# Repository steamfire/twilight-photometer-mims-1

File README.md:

View this project on [CADLAB.io](https://cadlab.io/project/26619). 

# twilight-photometer-mims-1
 Simple version of Forrest Mims 1 channel DIY twilight photometer

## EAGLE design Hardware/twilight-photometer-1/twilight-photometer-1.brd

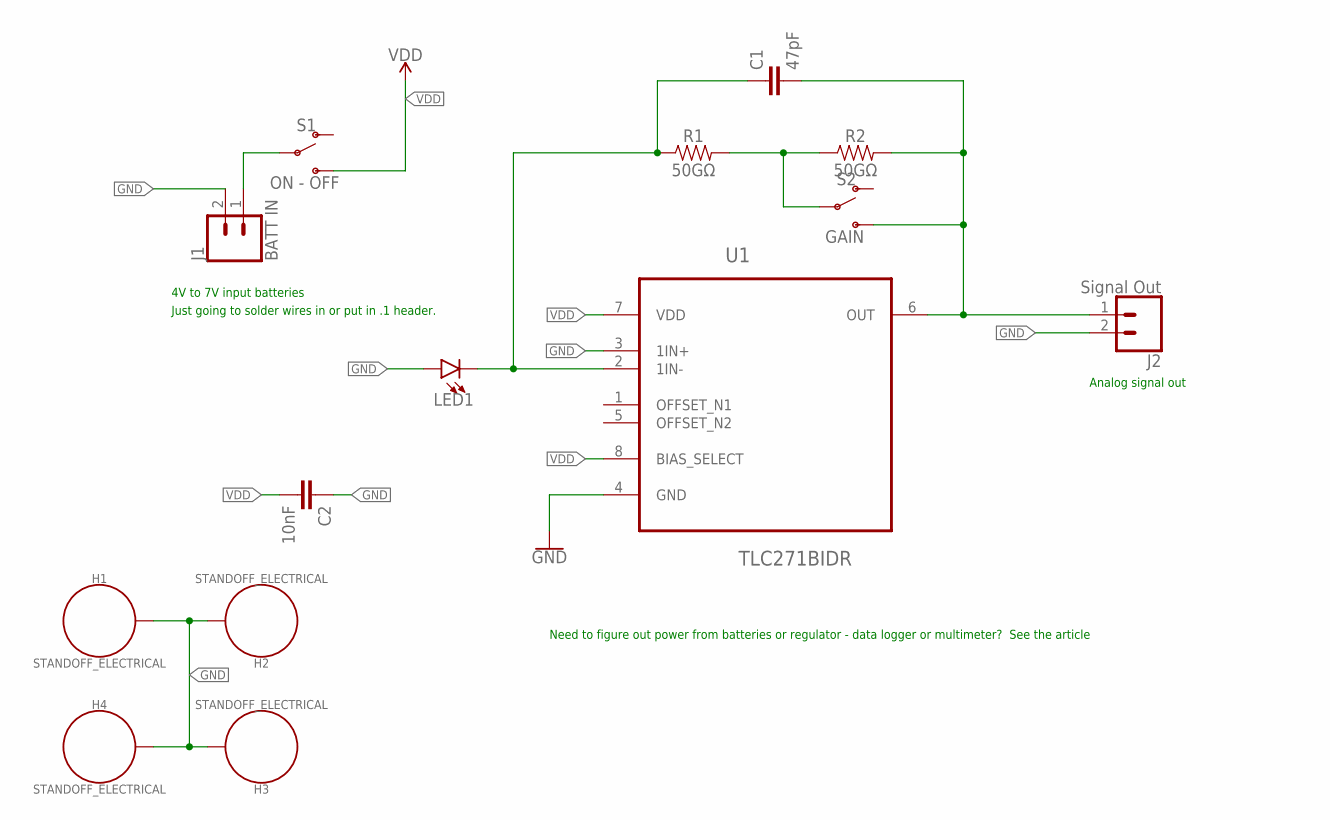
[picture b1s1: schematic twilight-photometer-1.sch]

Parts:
C1: 47pF; 0603
C2: 10nF; 0603
H1, H2, H3, H4: STANDOFF_ELECTRICAL; STANDOFF-ELECTRICAL
J1: BATT IN; 1X02_LOCK_LONGPADS
J2: Signal Out; 1X02_LOCK_LONGPADS
LED1: LED5MM; LED_5MM
R1, R2: 50GΩ; 0805
S1: ON - OFF; SWITCH_SPDT_PTH_11.6X4.0MM_LOCK
S2: GAIN; SWITCH_SPDT_PTH_11.6X4.0MM_LOCK
U1: TLC271BIDR; SOIC127P600X175-8N

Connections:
GND: C2.1, H1.P1, H2.P1, H3.P1, H4.P1, J1.2, J2.2, LED1.A, U1.3 (1IN+), U1.4 (GND)
unnamed: R1.2, R2.1, S2.2
unnamed: C1.1, LED1.K (C), R1.1, U1.2 (1IN-)
unnamed: J1.1, S1.2
unnamed: C1.2, J2.1, R2.2, S2.3 (S), U1.6 (OUT)
VDD: C2.2, S1.3 (S), U1.7 (VDD), U1.8 (BIAS_SELECT)

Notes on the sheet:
Need to figure out power from batteries or regulator - data logger or multimeter? See the article
4V to 7V input batteries
Just going to solder wires in or put in .1 header.
Analog signal out

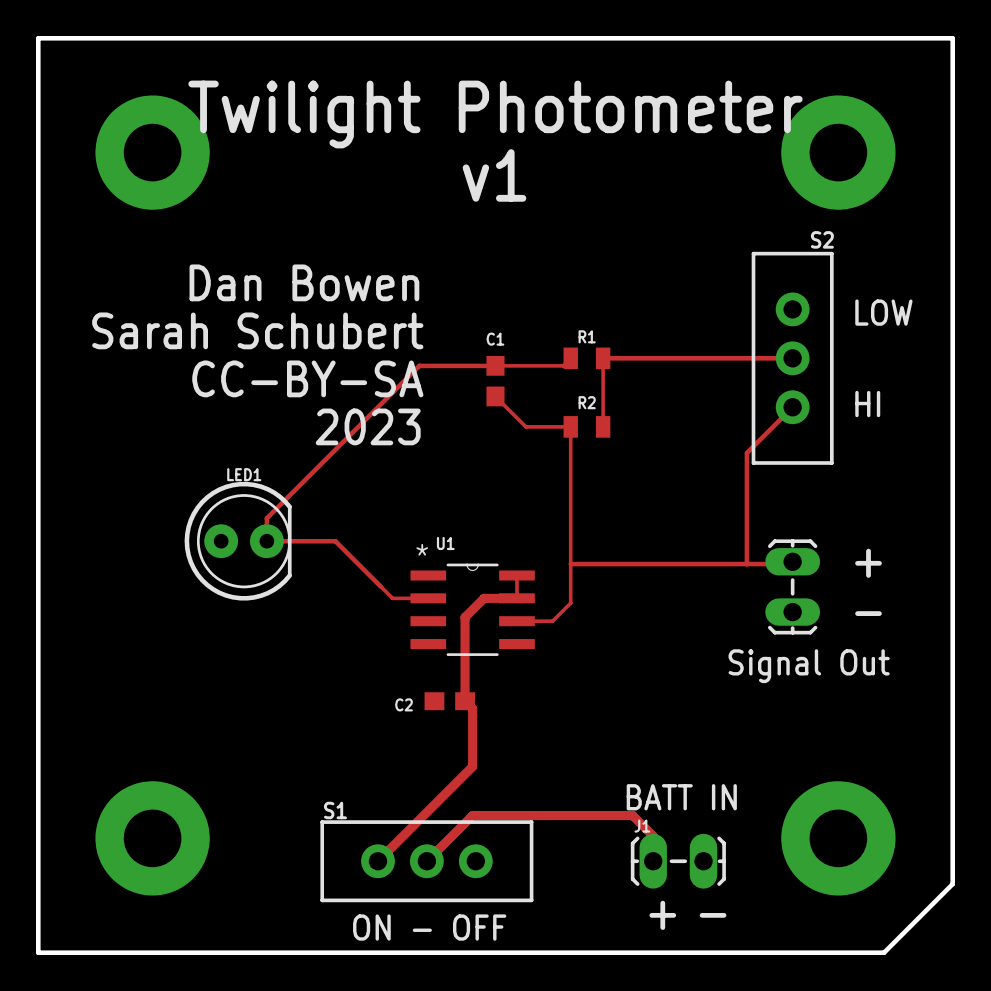
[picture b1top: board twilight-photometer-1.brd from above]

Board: 2 copper layers, 50.8 x 50.8 mm, 14 parts (0 on the bottom side), 6 nets.

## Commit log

2023-03-15 Added gitkeep to subfolders
2023-03-15 Backlink to CADLAB.io has been added.
2023-03-16 First layout on schematic
2023-03-16 Partial board layout
    Still need to finish circut schematic
2023-04-01 Finished routing, Board sizing for V1
2023-04-01 Adjusted for OSHpark optimization

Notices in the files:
Hardware/twilight-photometer-1/twilight-photometer-1.brd:
CC-BY-SA
parts and their libraries:
SparkFun-Capacitors: Licensing: Creative Commons ShareAlike 4.0 International - https://creativecommons.org/licenses/by-sa/4.0
